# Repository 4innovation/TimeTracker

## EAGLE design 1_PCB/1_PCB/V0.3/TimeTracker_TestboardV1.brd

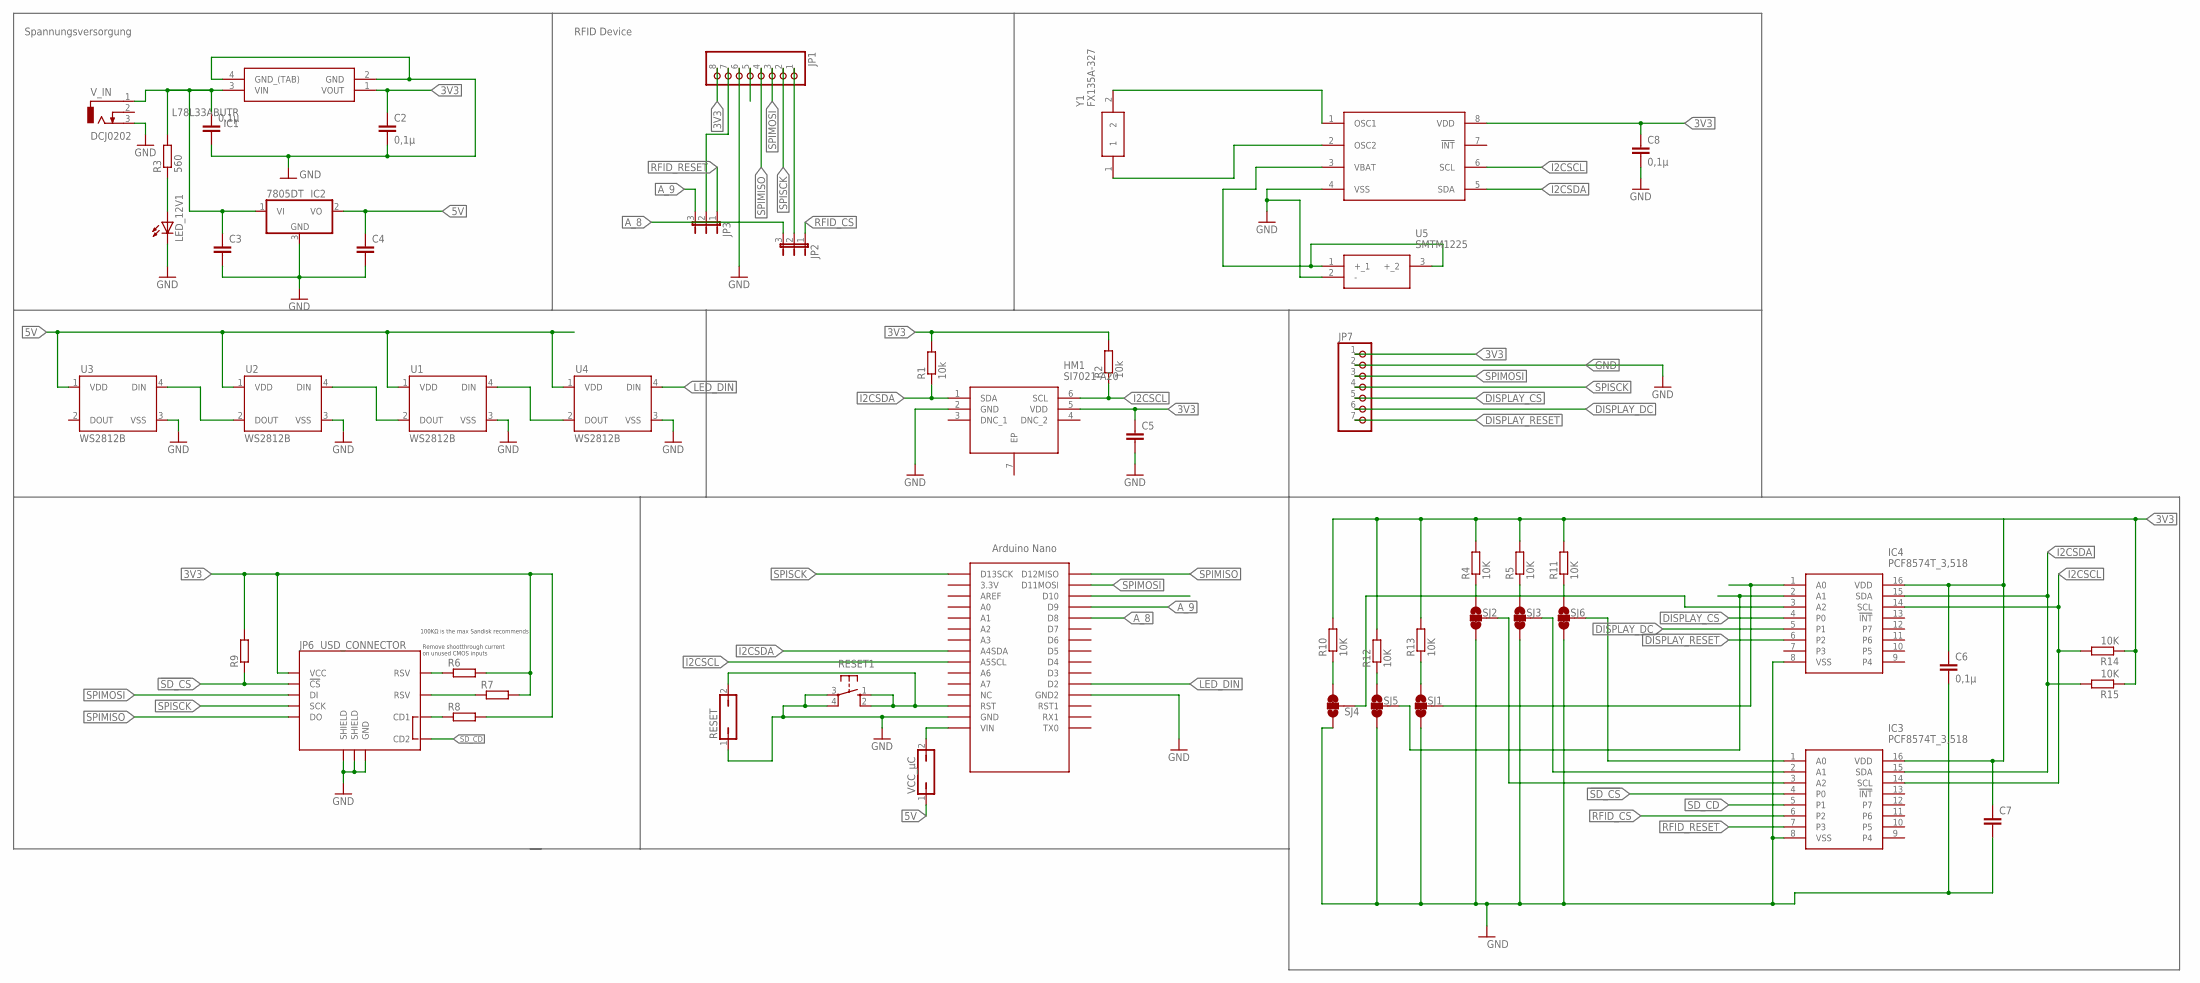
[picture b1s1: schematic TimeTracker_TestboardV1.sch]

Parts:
0.1µ: C-EUC0805; C0805
C2, C6, C8: 0,1µ; C0805
C3, C4, C5, C7: C-EUC0805; C0805
HM1: SI7021-A20; SON100P300X300X80-7N
IC1: L78L33ABUTR; ST-SOT-89
IC2: 7805DT; TO252
IC3, IC4: PCF8574T_3,518; SOIC127P1032X265-16N
JP1: PINHD-1X8; 1X08
JP2, JP3: JP2E; JP2
JP6: USD_CONNECTOR; MICRO-SD-SOCKET-PP
JP7: PINHD-1X7; 1X07
LED_12V1: LEDSML0805; SML0805
R1, R2: 10k; R0805
R3: 560; R0805
R4, R5, R10, R11, R12, R13, R14, R15: 10K; R0805
R6, R7, R8, R9: 100k; R0805
RESET: JP1Q; JP1
RESET1: 10-XX; B3F-10XX
SJ1, SJ2, SJ3, SJ4, SJ5, SJ6: JUMPER-PAD-3-2OF3_NC_BY_TRACE_SMALL; PAD-JUMPER-3-2OF3_NC_BY_TRACE_YES_SILK_FULL_BOX
U1, U2, U3, U4: WS2812B
U5: SMTM1225
U$1: NANO
U$2: RTC; SOP65P490X110-8N
VCC_µC: JP1Q; JP1
V_IN: DCJ0202
Y1: FX135A-327; FX135

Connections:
3V3: C2.1, C5.1, C6.1, C7.1, C8.1, HM1.5 (VDD), IC1.1 (VOUT), IC3.16 (VDD), IC4.16 (VDD), JP1.8, JP6.VCC, JP7.1, R1.2, R2.2, R4.2, R5.2, R6.2, R7.2, R8.2, R9.2, R10.2, R11.2, R12.2, R13.2, R14.1, R15.1, U$2.8 (VDD)
5V: C4.1, IC2.2 (VO), U1.1 (VDD), U2.1 (VDD), U3.1 (VDD), U4.1 (VDD), VCC_µC.1
!SD_CS: IC3.4 (P0), JP6.CS (!CS), R9.1
A_8: JP2.3, U$1.D8
A_9: JP3.3, U$1.D9
CDSDSD: JP6.CD1, R8.1
DISPLAY_CS: IC4.4 (P0), JP7.5
DISPLAY_DC: IC4.5 (P1), JP7.6
DISPLAY_RESET: IC4.6 (P2), JP7.7
EP: HM1.7 (EP)
GND: 0.1µ.2, C2.2, C3.2, C4.2, C5.2, C6.2, C7.2, C8.2, HM1.2 (GND), IC1.2 (GND), IC1.4 (GND_(TAB)), IC2.3 (GND), IC3.8 (VSS), IC4.8 (VSS), JP1.6, JP6.GND, JP6.GND1 (SHIELD), JP6.GND3 (SHIELD), JP7.2, LED_12V1.C, RESET.1, RESET1.3, RESET1.4 (P1), SJ1.3, SJ2.3, SJ3.3, SJ4.1, SJ5.3, SJ6.3, U1.3 (VSS), U2.3 (VSS), U3.3 (VSS), U4.3 (VSS), U5.2 (-), U$1.GND, U$1.GND1 (GND2), U$2.4 (VSS), V_IN.3
GND1: RESET.2, RESET1.1 (S), RESET1.2 (S1), U$1.RST
I2CSCL: HM1.6 (SCL), IC3.14 (SCL), IC4.14 (SCL), R2.1, R14.2, U$1.A5 (A5SCL), U$2.6 (SCL)
I2CSDA: HM1.1 (SDA), IC3.15 (SDA), IC4.15 (SDA), R1.1, R15.2, U$1.A4 (A4SDA), U$2.5 (SDA)
LED_DIN: U4.4 (DIN), U$1.D2
unnamed: 0.1µ.1, C3.1, IC1.3 (VIN), IC2.1 (VI), R3.2, V_IN.1
unnamed: JP1.1, JP2.2
unnamed: IC3.1 (A0), SJ6.2
unnamed: IC3.2 (A1), SJ3.2
unnamed: IC3.3 (A2), SJ2.2
unnamed: U1.4 (DIN), U4.2 (DOUT)
unnamed: U1.2 (DOUT), U2.4 (DIN)
unnamed: U2.2 (DOUT), U3.4 (DIN)
unnamed: U$1.RAW (VIN), VCC_µC.2
unnamed: U$2.1 (OSC1), Y1.2
unnamed: U$2.2 (OSC2), Y1.1
unnamed: U5.1 (+_1), U5.3 (+_2), U$2.3 (VBAT)
unnamed: IC4.1 (A0), SJ1.2
unnamed: IC4.2 (A1), SJ5.2
unnamed: IC4.3 (A2), SJ4.2
unnamed: R10.1, SJ4.3
unnamed: R11.1, SJ6.1
unnamed: R5.1, SJ3.1
unnamed: R4.1, SJ2.1
unnamed: R12.1, SJ5.1
unnamed: R13.1, SJ1.1
unnamed: JP1.7, JP3.2
unnamed: LED_12V1.A, R3.1
RFID_CS: IC3.6 (P2), JP2.1
RFID_RESET: IC3.7 (P3), JP3.1
RSV@1: JP6.RSV1 (RSV), R6.1
RSV@2: JP6.RSV2 (RSV), R7.1
SD_CD: IC3.5 (P1), JP6.CD2
SPIMISO: JP1.4, JP6.DO, U$1.D12 (D12MISO)
SPIMOSI: JP1.3, JP6.DI, JP7.3, U$1.D11 (D11MOSI)
SPISCK: JP1.2, JP6.SCLK (SCK), JP7.4, U$1.D13 (D13SCK)

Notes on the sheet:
Spannungsversorgung
RFID Device
Remove shootthrough current on unused CMOS inputs
100KΩ is the max Sandisk recommends

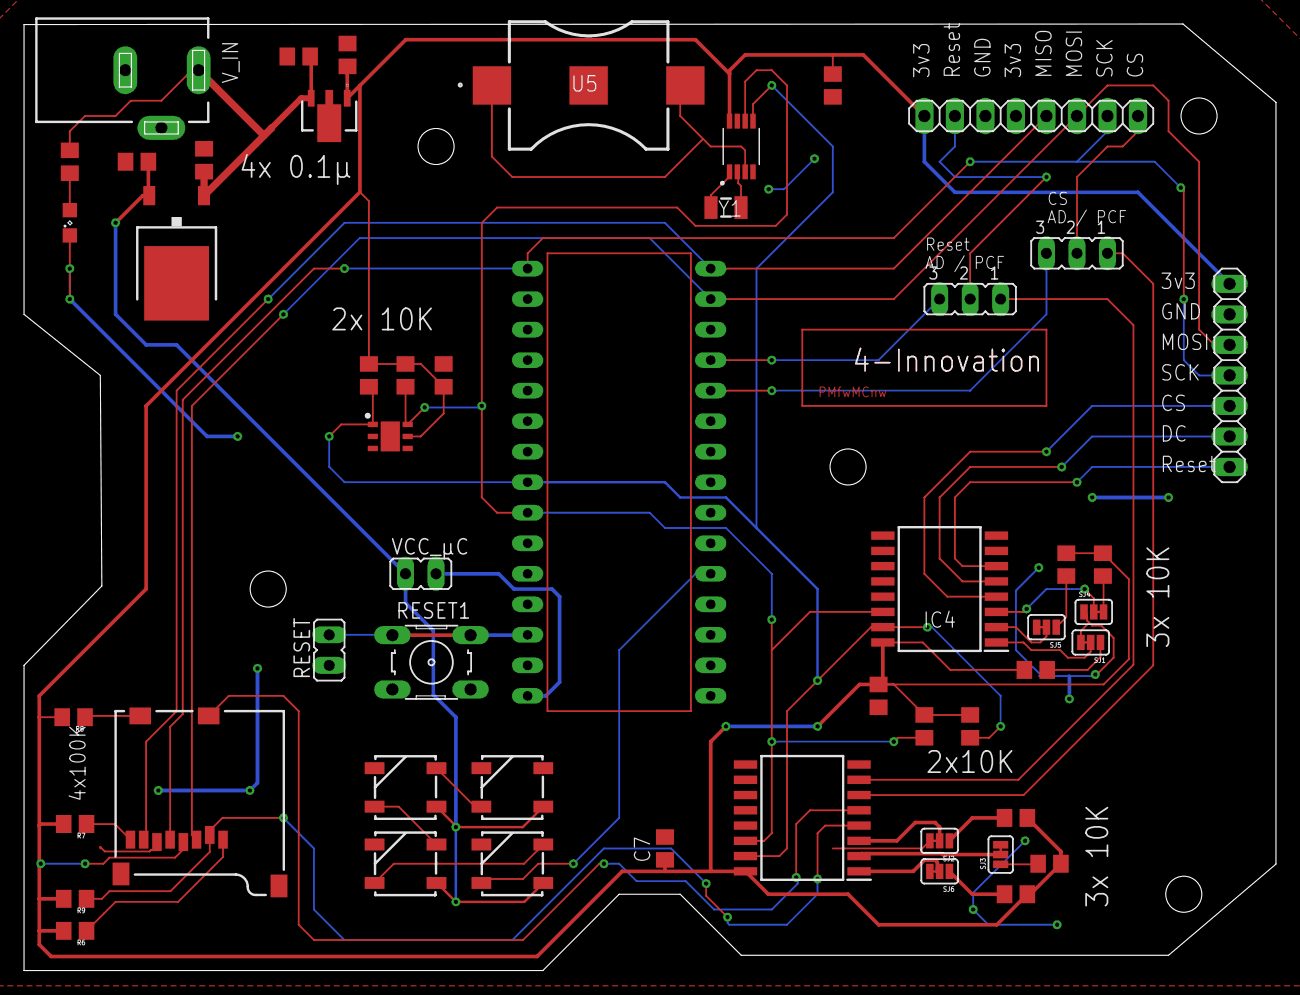
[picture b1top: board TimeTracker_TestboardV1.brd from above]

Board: 2 copper layers, 104.2 x 78.8 mm, 52 parts (0 on the bottom side), 45 nets.

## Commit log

2019-08-30 SetupRepository
2019-08-31 Fuxk u Raj
2019-09-01 fucvk u raj
2019-09-02 First Commit Mitun
2019-09-02 Battery Holder and Oscillator Added to circtuit
2019-09-02 Humidity and Temp Sensor
2019-09-02 Nico addition and modifications
2019-09-02 Nico
    Update PCB
2019-09-03 Added a new Voltage Regulator
2019-09-03 I/O Expander changed
2019-09-03 Nicolas
    update PCB
    PCB V0.2
2019-09-03 Nicolas
    PCB Update
2019-09-03 Nicolas
    Update PCB Ready for Production
2019-09-07 Nicolas
    kleine Fehlerkorrektur
2019-09-09 Nicolas
    Code Snipptes
2019-09-09 Nicolas
    Update
2019-09-09 Nicolas
    Setup TimeTracker GUI Software
2019-09-09 Nicolas
    GUI
    Multiple Form start
2019-09-09 Nicolas
    Update GUI
2019-10-04 Niolas Update
2019-10-04 Nicolas Update
2019-11-09 Nicolas Update GUI
2019-11-23 Nicolas Update Software GUI
2019-11-23 Nicolas Update Software - keine Lust mehr
2019-11-23 Nicolas

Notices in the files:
parts and their libraries:
SparkFun-LED: Licensing: CC v3.0 Share-Alike You are welcome to use this library for commercial purposes.
SparkFun-Aesthetics: Licensing: Creative Commons ShareAlike 4.0 International - https://creativecommons.org/licenses/by-sa/4.0
